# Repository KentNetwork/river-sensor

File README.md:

# river-sensor
A sensor for monitoring river levels based on the work by Oxford Flood Network: https://github.com/OxFloodNet/sensor-device
Requires BLE Peripheral firmware (at least 110.6.1.0) flashed on the device before uploading the smartbasic program. 
You may have to use the SWD interface to do this as soft device can't be flashed via UART.

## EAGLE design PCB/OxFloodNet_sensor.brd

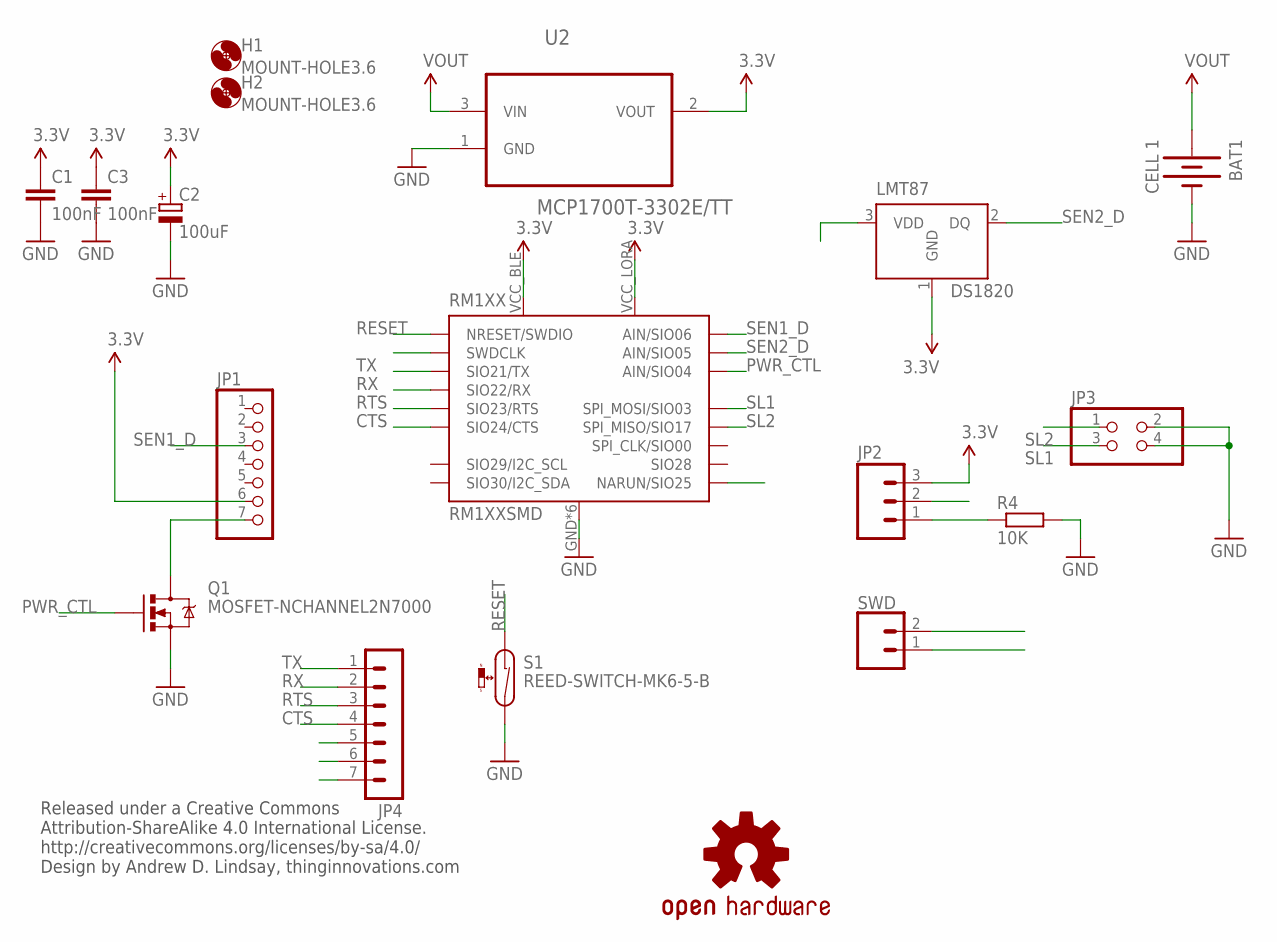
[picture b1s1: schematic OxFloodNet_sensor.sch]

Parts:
BAT1: CELL 1; BATTERY-AA
C1, C3: 100nF; C025-024X044
C2: 100uF; E2,5-6E
H1, H2: MOUNT-HOLE3.6; 3,6
JP1: 1X07
JP2: M03PTH; 1X03
JP3: 2X02
JP4: MA07-1
LMT87: DS1820; TO-92
LOGO1: OSHW-LOGOM; OSHW-LOGO-M
Q1: MOSFET-NCHANNEL2N7000; TO-92
R4: 10K; R0603
RM1XX: RM1XXSMD; RM1XX
S1: REED-SWITCH-MK6-5-B; MK6-5
SWD: CONN_02; 1X02
U2: MCP1700T-3302E/TT; SOT95P237X112-3N

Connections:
3.3V: C1.1, C2.+, C3.1, JP1.6, JP2.3, JP4.6, LMT87.1 (GND), RM1XX.VCC_BLE, RM1XX.VCC_LORA, U2.2 (VOUT)
ARUN: JP2.2, RM1XX.SIO25 (NARUN/SIO25)
CTS: JP4.4, RM1XX.SIO24 (SIO24/CTS)
GND: BAT1.GND@1 (-), C1.2, C2.-, C3.2, JP3.2, JP3.4, JP4.5, Q1.1 (S), R4.2, RM1XX.GND, RM1XX.GND1 (GND), RM1XX.GND2 (GND), RM1XX.GND3 (GND), RM1XX.GND4 (GND), RM1XX.GND5 (GND), S1.2, U2.1 (GND)
unnamed: JP2.1, R4.1
unnamed: JP1.7, LMT87.3 (VDD), Q1.3 (D)
PWR_CTL: Q1.2 (G), RM1XX.SIO04 (AIN/SIO04)
RESET: RM1XX.RESET (NRESET/SWDIO), S1.1, SWD.2
RTS: JP4.3, RM1XX.SIO23 (SIO23/RTS)
RX: JP4.2, RM1XX.SIO22 (SIO22/RX)
SEN1_D: JP1.3, RM1XX.SIO06 (AIN/SIO06)
SEN2_D: LMT87.2 (DQ), RM1XX.SIO05 (AIN/SIO05)
SL1: JP3.3, RM1XX.SIO03 (SPI_MOSI/SIO03)
SL2: JP3.1, RM1XX.SIO17 (SPI_MISO/SIO17)
SWDCLK: RM1XX.SWDCLK, SWD.1
TX: JP4.1, RM1XX.SIO21 (SIO21/TX)
VOUT: BAT1.PWR@1 (+), JP4.7, U2.3 (VIN)

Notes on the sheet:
Released under a Creative Commons Attribution-ShareAlike 4.0 International License. http://creativecommons.org/licenses/by-sa/4.0/ Design by Andrew D. Lindsay, thinginnovations.com

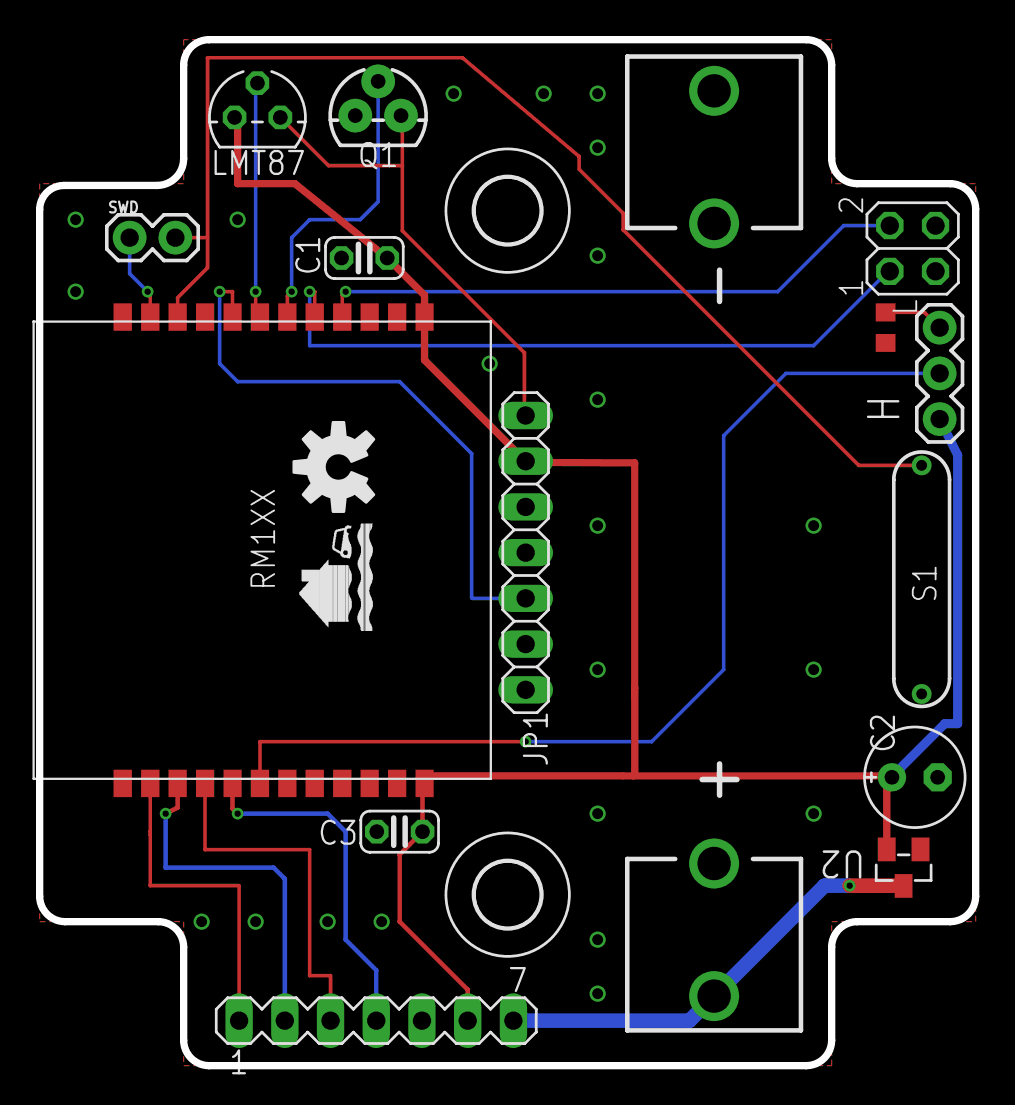
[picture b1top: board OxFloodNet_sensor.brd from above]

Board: 2 copper layers, 52.0 x 57.0 mm, 18 parts (0 on the bottom side), 17 nets.

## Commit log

2018-05-02 updated program with ble and begininngs of temperature compensation

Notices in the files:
parts and their libraries:
SparkFun-DiscreteSemi: Licensing: CC v3.0 Share-Alike You are welcome to use this library for commercial purposes.
SparkFun-Connectors: Licensing: Creative Commons ShareAlike 4.0 International - https://creativecommons.org/licenses/by-sa/4.0
